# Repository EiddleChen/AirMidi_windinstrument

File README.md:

AirMidi is the simplify and extend of
the Arduino platform, with the powerful Arduion library , the control of MIDI come to flexible
and simple.Moreover, with the LUFA framework, the development cost of USB protcool get
prodigious reduce, so the project can also simulate other USB device such as USB keyboard or
USB mouse.

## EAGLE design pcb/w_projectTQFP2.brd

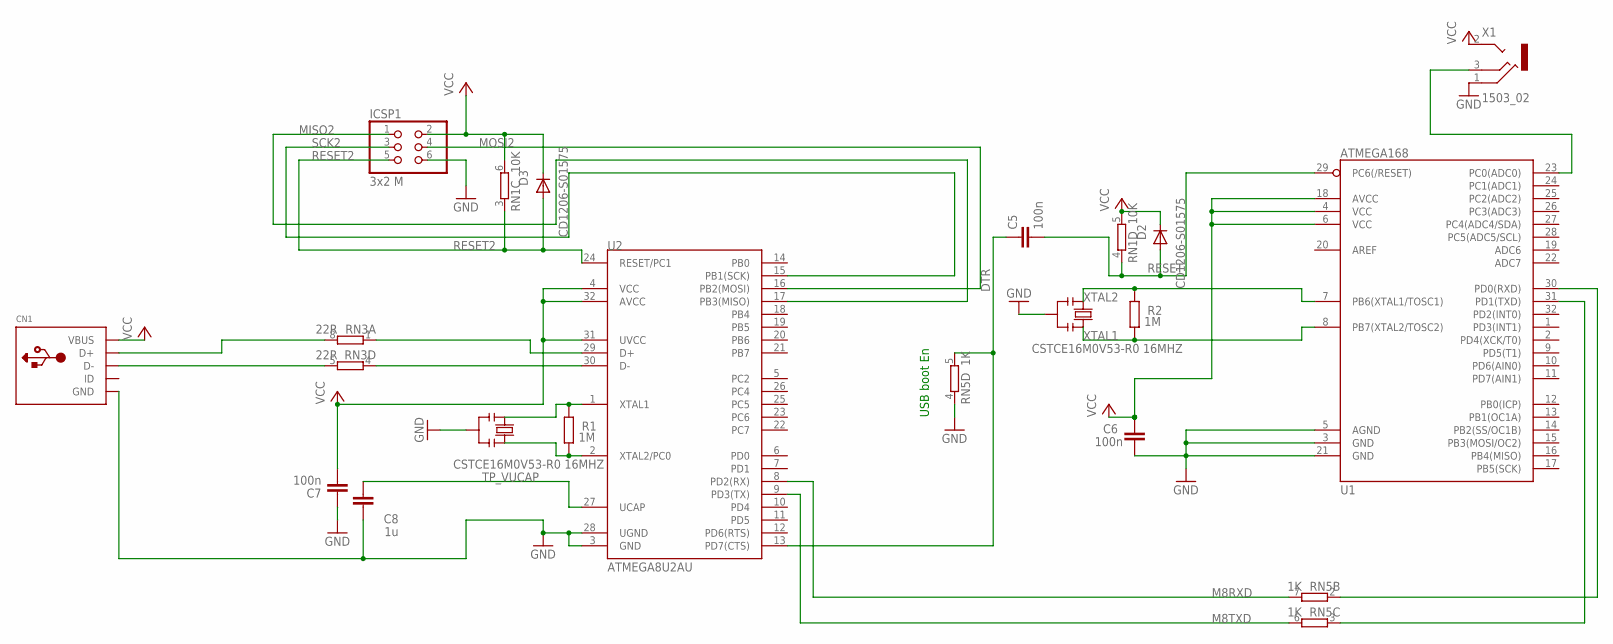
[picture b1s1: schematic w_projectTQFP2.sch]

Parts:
C5, C6, C7: 100n; C0603-ROUND; MPN 06033G104ZAT2A
C8: 1u; C0603-ROUND; MPN 1206YC105KAT2A
CN1: USBMINIB; USB-MINIB; MPN 67503-1030
D2, D3: CD1206-S01575; MINIMELF; MPN CD1206-S01575
ICSP1: 3x2 M; 2X03
R1, R2: 1M; R0603-ROUND; MPN CR0603-JW-105GLF
RN1: 10K; CAY16; MPN CAY16-1002F4LF.
RN3: 22R; CAY16; MPN CAY16-220J4LF
RN5: 1K; CAY16; MPN CAY16-102J4LF
U1: ATMEGA168; TQFP32-08; MPN ATMEGA328P-AU
U2: ATMEGA8U2AU; TQFP32-08; MPN ATMEGA16U2-AU
X1: 1503_02; MPN 1503 02
Y2, Y4: CSTCE16M0V53-R0 16MHZ; RESONATOR; MPN CSTCE16M0V53-R0

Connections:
D+: CN1.D+, RN3.8 (2)
DTR: C5.1, RN5.5 (2), U2.13 (PD7(CTS))
GND: C6.1, C7.2, C8.2, CN1.GND, ICSP1.6, RN5.4 (1), U1.3 (GND), U1.5 (AGND), U1.21 (GND), U2.3 (GND), U2.28 (UGND), X1.1, Y2.2, Y4.2
IO1: RN5.3 (1), U1.31 (PD1(TXD))
M8RXD: RN5.7 (2), U2.8 (PD2(RX))
M8TXD: RN5.6 (2), U2.9 (PD3(TX))
MISO2: ICSP1.1, U2.17 (PB3(MISO))
MOSI2: ICSP1.4, U2.16 (PB2(MOSI))
unnamed: RN5.2 (1), U1.30 (PD0(RXD))
unnamed: U1.23 (PC0(ADC0)), X1.3
unnamed: RN3.1, U2.29 (D+)
unnamed: CN1.D-, RN3.5 (2)
unnamed: R1.1, U2.2 (XTAL2/PC0), Y4.3
unnamed: RN3.4 (1), U2.30 (D-)
unnamed: R1.2, U2.1 (XTAL1), Y4.1
RESET: C5.2, D2.A, RN1.4 (1), U1.29 (PC6(/RESET))
RESET2: D3.A, ICSP1.5, RN1.3 (1), U2.24 (RESET/PC1)
SCK2: ICSP1.3, U2.15 (PB1(SCK))
TP_VUCAP: C8.1, U2.27 (UCAP)
VCC: C6.2, C7.1, CN1.VBUS, D2.C, D3.C, ICSP1.2, RN1.5 (2), RN1.6 (2), U1.4 (VCC), U1.6 (VCC), U1.18 (AVCC), U2.4 (VCC), U2.31 (UVCC), U2.32 (AVCC), X1.2
XTAL1: R2.1, U1.8 (PB7(XTAL2/TOSC2)), Y2.3
XTAL2: R2.2, U1.7 (PB6(XTAL1/TOSC1)), Y2.1

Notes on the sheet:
USB boot En

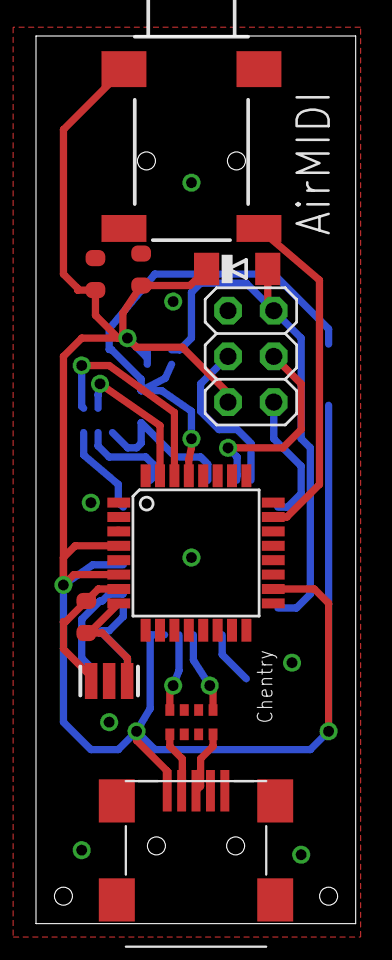
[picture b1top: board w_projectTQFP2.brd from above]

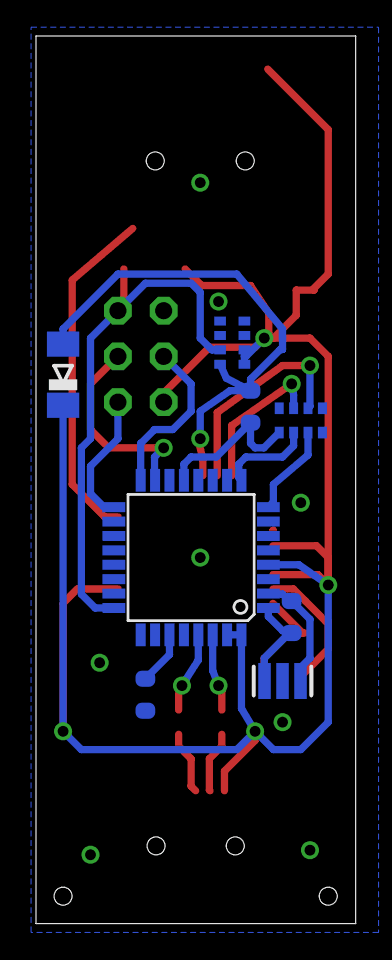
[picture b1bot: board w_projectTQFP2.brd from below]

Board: 2 copper layers, 17.8 x 49.3 mm, 18 parts (8 on the bottom side), 22 nets.

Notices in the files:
parts and their libraries:
SparkFun: Licensing: CC v3.0 Share-Alike You are welcome to use this library for commercial purposes.
